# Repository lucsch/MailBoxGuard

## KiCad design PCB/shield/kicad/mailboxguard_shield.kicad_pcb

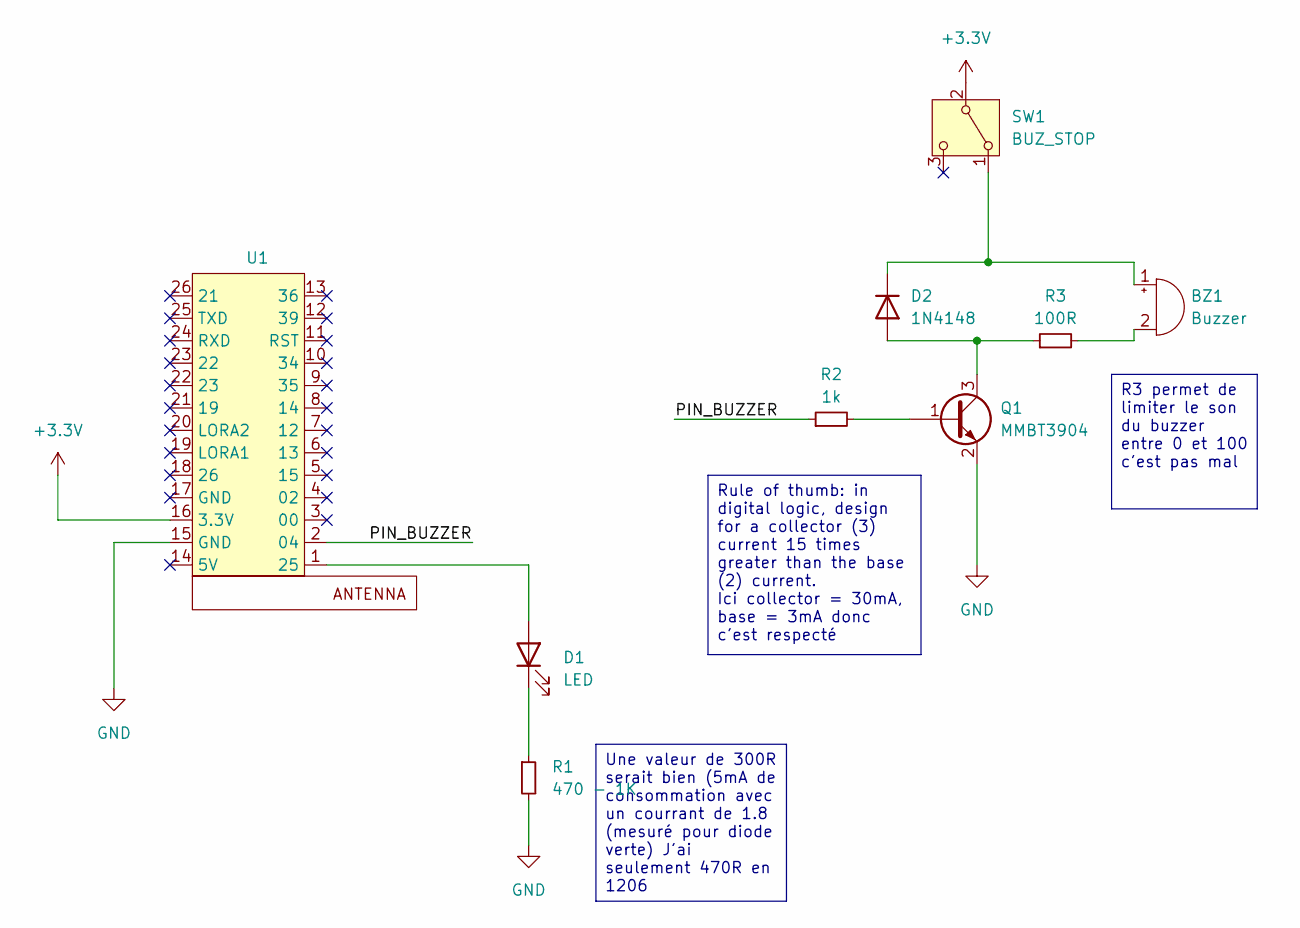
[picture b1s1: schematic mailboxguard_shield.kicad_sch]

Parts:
BZ1: Buzzer; Buzzer_12x9.5RM7.6
D1: LED; LED_D5.0mm
D2: 1N4148; D_MiniMELF
Q1: MMBT3904; SOT-23
R1: 470 - 1K; R_1206_3216Metric
R2: 1k; R_1206_3216Metric
R3: 100R; R_1206_3216Metric
SW1: BUZ_STOP; SLIDE SWITCH
U1: Lilygo TTGO Lora32 shield

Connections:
+3.3V: SW1.2 (B), U1.16 (3.3V)
/PIN_BUZZER: R2.1, U1.2 (04)
GND: Q1.2 (E), R1.2, U1.15 (GND)
unnamed: BZ1.1 (+), D2.1 (K), SW1.1 (A)
unnamed: BZ1.2 (-), R3.2
unnamed: D1.2 (A), U1.1 (25)
unnamed: D1.1 (K), R1.1
unnamed: D2.2 (A), Q1.3 (C), R3.1
unnamed: Q1.1 (B), R2.2

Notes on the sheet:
Une valeur de 300R serait bien (5mA de consommation avec un courrant de 1.8 (mesuré pour diode verte) J'ai seulement 470R en 1206
R3 permet de limiter le son du buzzer entre 0 et 100 c'est pas mal
Rule of thumb: in digital logic, design for a collector (3) current 15 times greater than the base (2) current. Ici collector = 30mA, base = 3mA donc c'est respecté

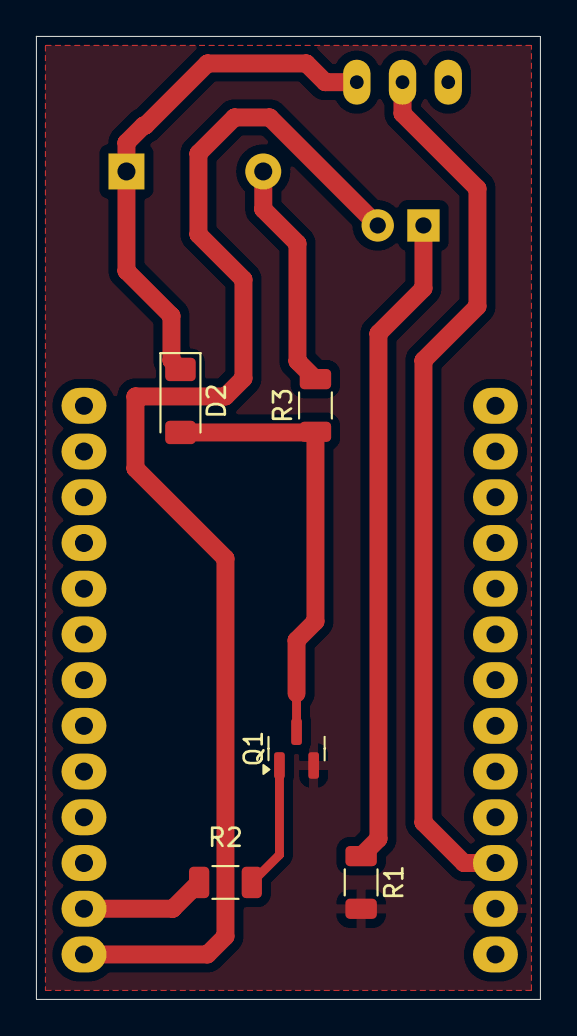
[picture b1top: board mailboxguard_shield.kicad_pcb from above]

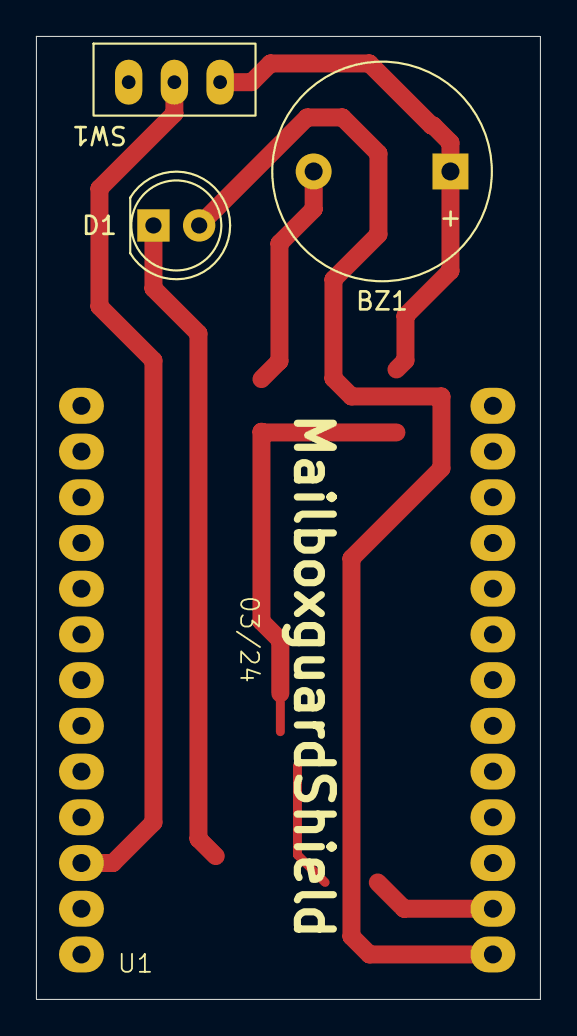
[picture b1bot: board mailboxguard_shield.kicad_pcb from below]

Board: 2 copper layers, 28.0 x 53.5 mm, 9 parts (4 on the bottom side), 9 nets.

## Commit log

2023-08-23 Adding LCSC parts number
2023-08-26 Updating LCSC parts number
2023-10-11 Adding sensor platformio project
2023-10-12 Updating code for the sensor (platformio version)
2023-10-12 Updating platformio code for gateway
2023-10-12 Adding serial logging for sensor
2023-10-13 Adding test code for serial port
2023-11-12 Adding code for uploading using pymcuprog
2023-11-12 Updating BOM
2023-11-29 Updating code to sensor is now working
2023-11-30 Correcting platformio code for setting clock speed to 5 MHZ
2024-03-07 Schema for Lora shield
2024-03-10 Buzzer shield is now finished
2024-03-10 Updating GERBER files for shield
2024-03-17 Updating SVG files for PCB
2024-09-25 Adding 3D files for battery support
2024-09-26 Adding 3D file for enclosure
2024-09-26 Correcting design for PCB support
2026-03-07 Updating 3d files
